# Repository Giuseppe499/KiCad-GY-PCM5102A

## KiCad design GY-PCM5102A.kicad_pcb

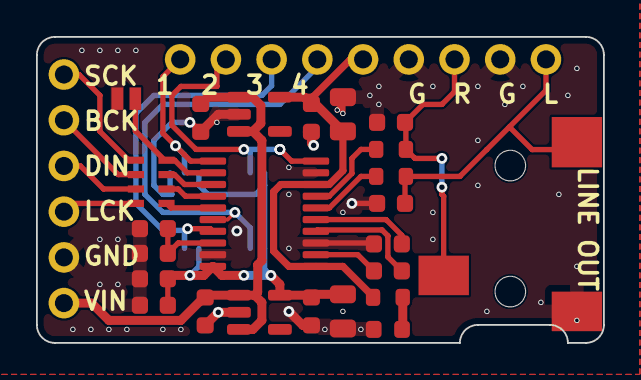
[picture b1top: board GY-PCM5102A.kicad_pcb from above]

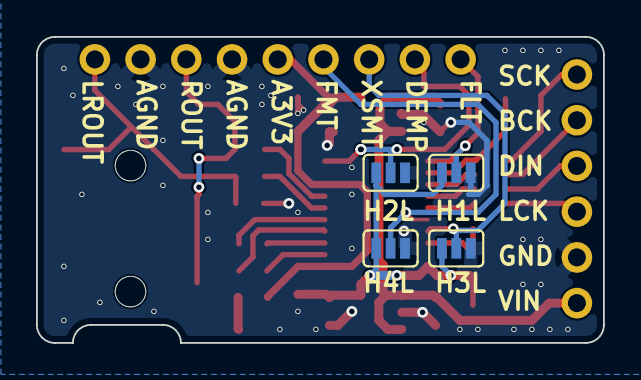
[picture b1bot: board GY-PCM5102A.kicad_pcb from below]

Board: 2 copper layers, 31.5 x 17.0 mm, 30 parts (4 on the bottom side), 25 nets.

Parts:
C1, C2, C4, C6, C12, C14: 100n; C_0603_1608Metric
C3, C5: 10u; C_0805_2012Metric
C7, C8, C9, C10: 2.2u; C_0603_1608Metric
C11, C13: 10u; C_0603_1608Metric
D1: Red; LED_0603_1608Metric
H1L, H2L, H3L, H4L: SolderJumper-3_P1.3mm_Open_Pad0.55x1.15mm
J1: M-BUS; PinHeader_1x06_P2.54mm_Vertical
J2: FUN_AND_OUT; PinHeader_1x09_P2.54mm_Vertical
J3: AudioJack3; Jack_3.5mm_CUI_SJ-3523-SMT_Horizontal
JP1: SolderJumper_2_Open; SolderJumper-2_P1.3mm_Open_Pad1.0x1.5mm
R1: 1K; R_0603_1608Metric
R2, R3: 470; R_0603_1608Metric
RN1: 22; R_Array_Concave_4x0603
U1: PCM5102A; TSSOP-20_4.4x6.5mm_P0.65mm
U2, U3: ME6211C33M5; SOT-23-5

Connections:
/AVDD: C2.1, C3.1, J2.5 (A3V3), R1.2, U1.1 (CPVDD), U1.8 (AVDD), U2.5 (V_{OUT})
/BCK: J1.5 (BCK), RN1.6 (R3.2)
/DEMP: H2L.2 (C), J2.2 (DEMP), U1.10 (DEMP)
/DIN: J1.4 (DIN), RN1.7 (R2.2)
/DVDD: C5.1, C6.1, C13.1, C14.2, H1L.1 (A), H2L.1 (A), H3L.1 (A), H4L.1 (A), U1.20 (DVDD), U3.5 (V_{OUT})
/FLT: H1L.2 (C), J2.1 (FLT), U1.11 (FLT)
/FMT: H4L.2 (C), J2.4 (FMT), U1.16 (FMT)
/LRCK: J1.3 (LRCK), RN1.8 (R1.2)
/OUTL: C9.1, J2.9 (LOUT), J3.T, R2.2
/OUTR: C10.1, J2.7 (ROUT), J3.R, R3.2
/SCK: J1.6 (SCK), RN1.5 (R4.2)
/VIN: C1.1, C4.1, J1.1 (VIN), U2.1 (V_{IN}), U2.3 (CE), U3.1 (V_{IN}), U3.3 (CE)
/XSMT: H3L.2 (C), J2.3 (XSMT), U1.17 (XSMT)
GND: C1.2, C2.2, C3.2, C4.2, C5.2, C6.2, C7.2, C9.2, C10.2, C11.2, C12.2, C13.2, C14.1, D1.1 (K), H1L.3 (B), H2L.3 (B), H3L.3 (B), H4L.3 (B), J1.2 (GND), J2.6 (AGND), J2.8 (AGND), J3.S, JP1.1 (A), U1.3 (CPGND), U1.9 (AGND), U1.19 (DGND), U2.2 (V_{SS}), U3.2 (V_{SS})
unnamed: D1.2 (A), R1.1
unnamed: JP1.2 (B), RN1.4 (R4.1), U1.12 (SCK)
unnamed: RN1.1 (R1.1), U1.15 (LRCK)
unnamed: RN1.2 (R2.1), U1.14 (DIN)
unnamed: RN1.3 (R3.1), U1.13 (BCK)
unnamed: C8.2, U1.4 (CAPM)
unnamed: C8.1, U1.2 (CAPP)
unnamed: C11.1, C12.1, U1.18 (LDOO)
unnamed: R2.1, U1.6 (OUTL)
unnamed: R3.1, U1.7 (OUTR)
unnamed: C7.1, U1.5 (VNEG)
